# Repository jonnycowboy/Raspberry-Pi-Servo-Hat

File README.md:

Raspberry-Pi-Servo-Hat
======================
Will contain:
- 16 channels of PWM / Servo Control
- RS485 Servo Control
- CAN BUS communication
- - can berry
- -  http://skpang.co.uk/catalog/pican-canbus-board-for-raspberry-pi-p-1196.html
- I2C Communication

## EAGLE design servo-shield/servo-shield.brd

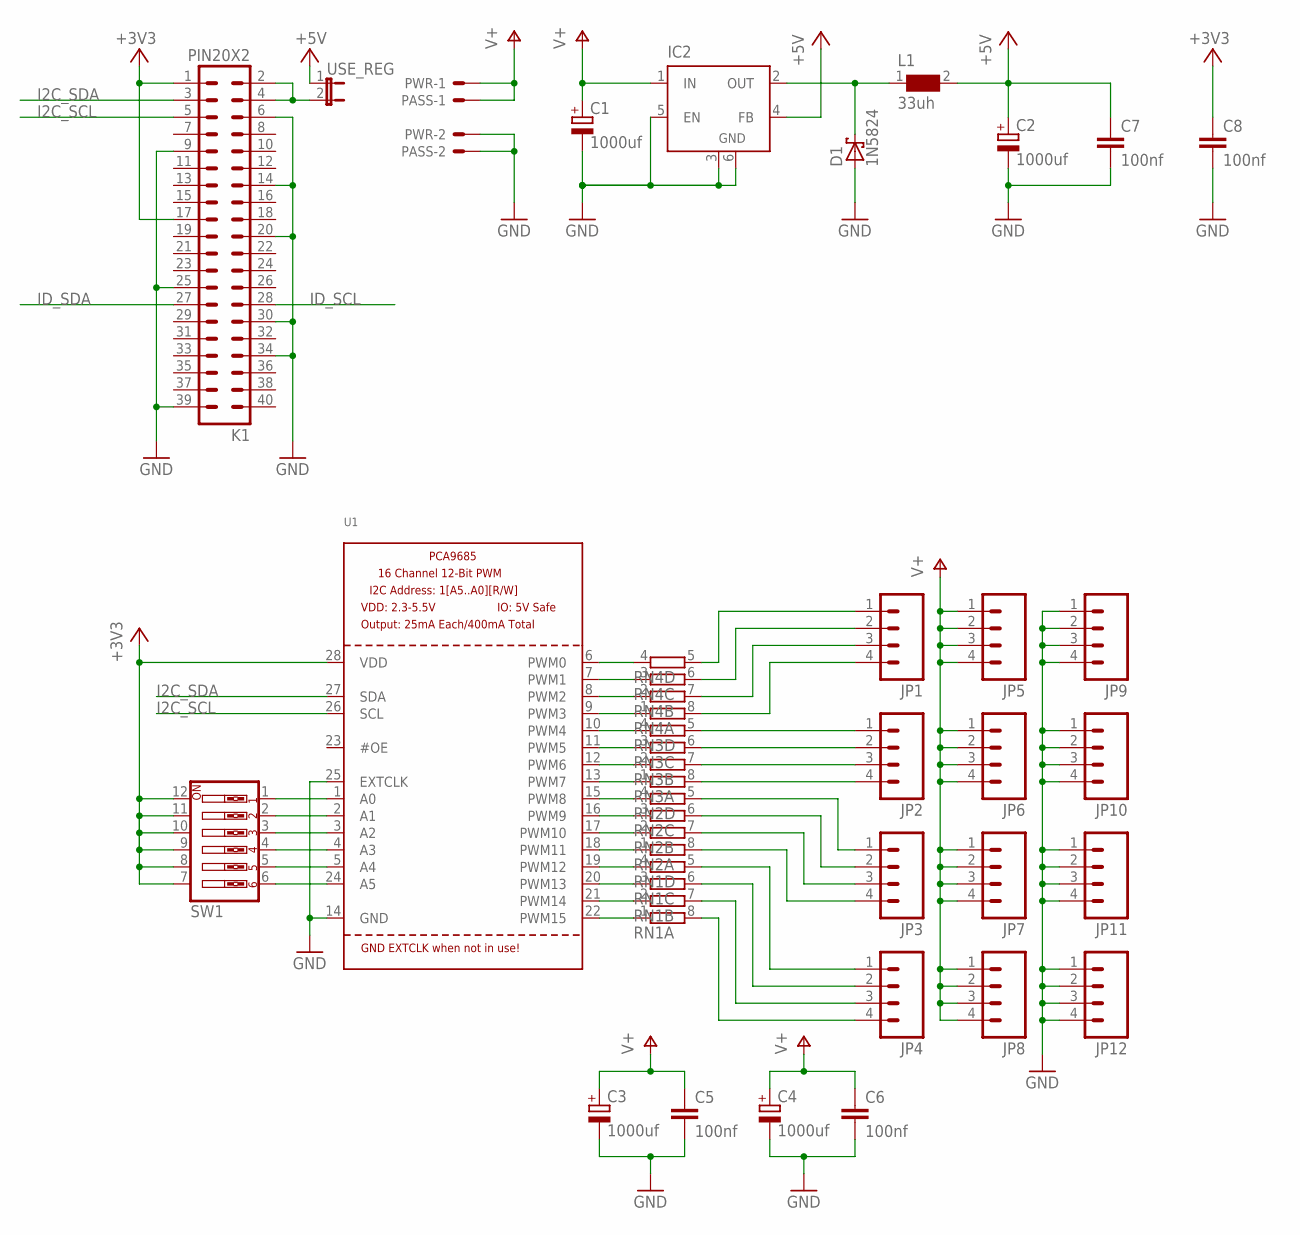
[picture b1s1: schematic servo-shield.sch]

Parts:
C1, C2, C3, C4: 1000uf; E3,5-8
C5, C6, C7, C8: 100nf; C025-030X050
D1: 1N5824; DO41-7.6
IC2: LM2596S; TO263-5
JP1, JP2, JP3, JP4, JP5, JP6, JP7, JP8, JP9, JP10, JP11, JP12: M04LOCK; 1X04_LOCK
K1: PIN20X2; PIN_20X2
L1: 33uh; WE-PD_1260/1245/1280/1210
PASS: 22-05-7028-02; 7395-02
PWR: 22-05-7028-02; 7395-02
RN1, RN2, RN3, RN4: 4R-NEXB38V; EXB38V
SW1: SW_DIP-6; EDG-06
U1: PCA9685; TSSOP28
USE_REG: JP1E; JP1

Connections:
+3V3: C8.1, K1.1, K1.17, SW1.7, SW1.8, SW1.9, SW1.10, SW1.11, SW1.12, U1.28 (VDD)
+5V: C2.+, C7.1, IC2.4 (FB), L1.2, USE_REG.1
GND: C1.-, C2.-, C3.-, C4.-, C5.2, C6.2, C7.2, C8.2, D1.A, IC2.3 (GND), IC2.5 (EN), IC2.6 (GND), JP9.1, JP9.2, JP9.3, JP9.4, JP10.1, JP10.2, JP10.3, JP10.4, JP11.1, JP11.2, JP11.3, JP11.4, JP12.1, JP12.2, JP12.3, JP12.4, K1.6, K1.9, K1.14, K1.20, K1.25, K1.30, K1.34, K1.39, PASS.2, PWR.2, U1.14 (GND), U1.25 (EXTCLK)
I2C_SCL: K1.5, U1.26 (SCL)
I2C_SDA: K1.3, U1.27 (SDA)
ID_SCL: K1.28
ID_SDA: K1.27
unnamed: RN2.3 (1), U1.16 (PWM9)
unnamed: RN2.4 (1), U1.15 (PWM8)
unnamed: RN3.1, U1.13 (PWM7)
unnamed: SW1.6, U1.24 (A5)
unnamed: JP1.4, RN4.8 (2)
unnamed: JP1.3, RN4.7 (2)
unnamed: JP1.2, RN4.6 (2)
unnamed: JP1.1, RN4.5 (2)
unnamed: JP3.1, RN2.5 (2)
unnamed: JP3.2, RN2.6 (2)
unnamed: SW1.1, U1.1 (A0)
unnamed: SW1.2, U1.2 (A1)
unnamed: SW1.5, U1.5 (A4)
unnamed: SW1.3, U1.3 (A2)
unnamed: SW1.4, U1.4 (A3)
unnamed: K1.2, K1.4, USE_REG.2
unnamed: JP3.3, RN2.7 (2)
unnamed: JP3.4, RN2.8 (2)
unnamed: JP4.1, RN1.5 (2)
unnamed: JP4.2, RN1.6 (2)
unnamed: JP4.3, RN1.7 (2)
unnamed: JP4.4, RN1.8 (2)
unnamed: RN1.1, U1.22 (PWM15)
unnamed: RN1.2 (1), U1.21 (PWM14)
unnamed: RN1.3 (1), U1.20 (PWM13)
unnamed: RN1.4 (1), U1.19 (PWM12)
unnamed: RN2.1, U1.18 (PWM11)
unnamed: RN2.2 (1), U1.17 (PWM10)
unnamed: RN3.2 (1), U1.12 (PWM6)
unnamed: RN3.3 (1), U1.11 (PWM5)
unnamed: RN3.4 (1), U1.10 (PWM4)
unnamed: RN4.1, U1.9 (PWM3)
unnamed: RN4.2 (1), U1.8 (PWM2)
unnamed: RN4.3 (1), U1.7 (PWM1)
unnamed: RN4.4 (1), U1.6 (PWM0)
unnamed: JP2.1, RN3.5 (2)
unnamed: JP2.4, RN3.8 (2)
unnamed: JP2.3, RN3.7 (2)
unnamed: JP2.2, RN3.6 (2)
V+: C1.+, C3.+, C4.+, C5.1, C6.1, IC2.1 (IN), JP5.1, JP5.2, JP5.3, JP5.4, JP6.1, JP6.2, JP6.3, JP6.4, JP7.1, JP7.2, JP7.3, JP7.4, JP8.1, JP8.2, JP8.3, JP8.4, PASS.1, PWR.1
VOUT: D1.C, IC2.2 (OUT), L1.1

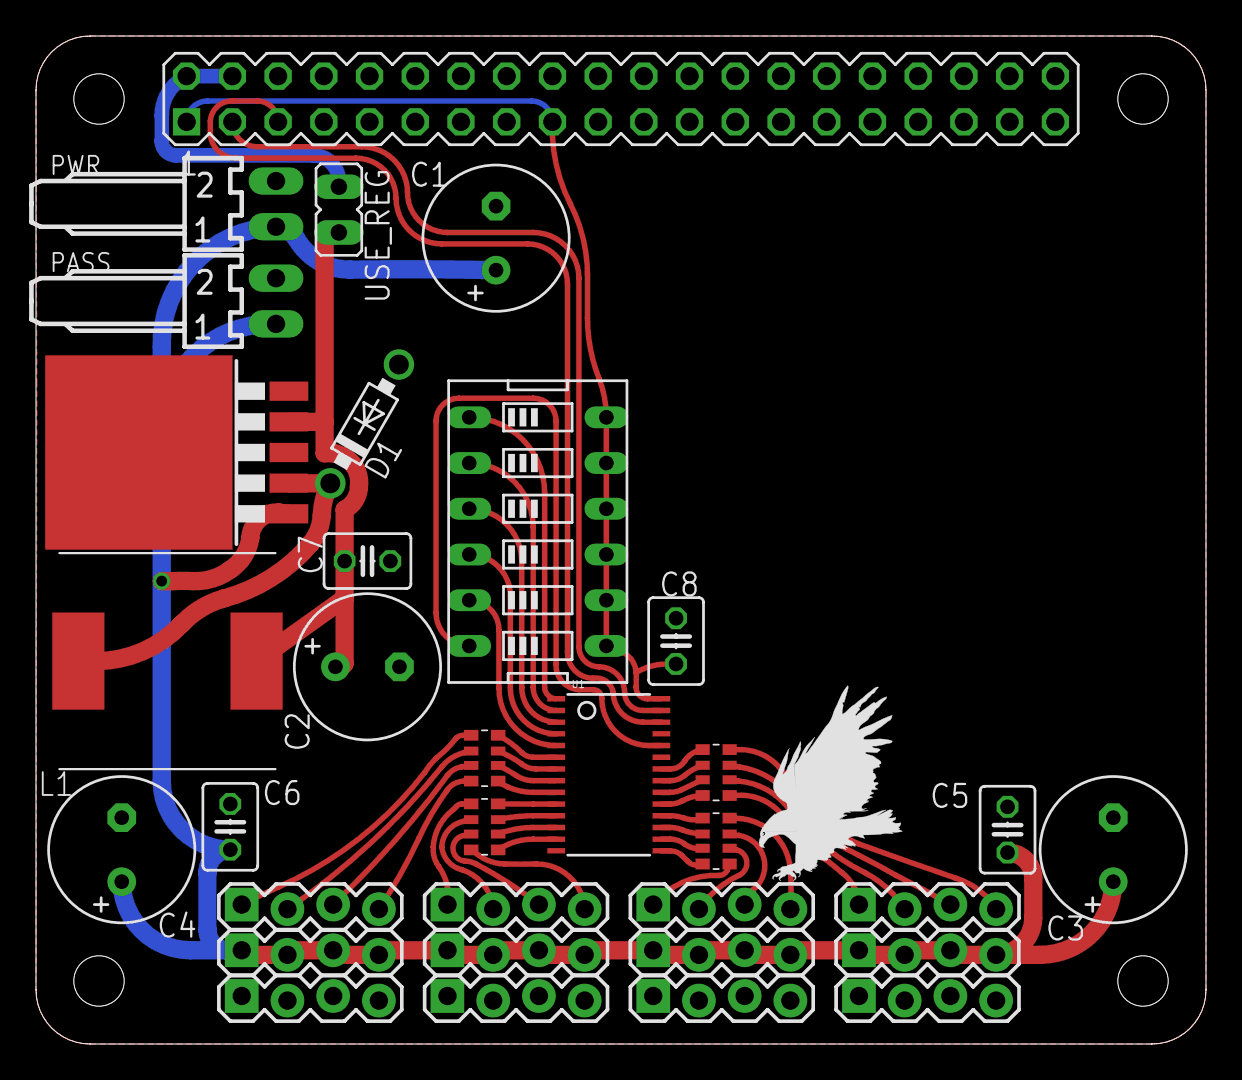
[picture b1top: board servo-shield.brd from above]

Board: 2 copper layers, 65.0 x 56.0 mm, 34 parts (0 on the bottom side), 46 nets.

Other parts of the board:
U$1: EAGLE-PLC-8MM

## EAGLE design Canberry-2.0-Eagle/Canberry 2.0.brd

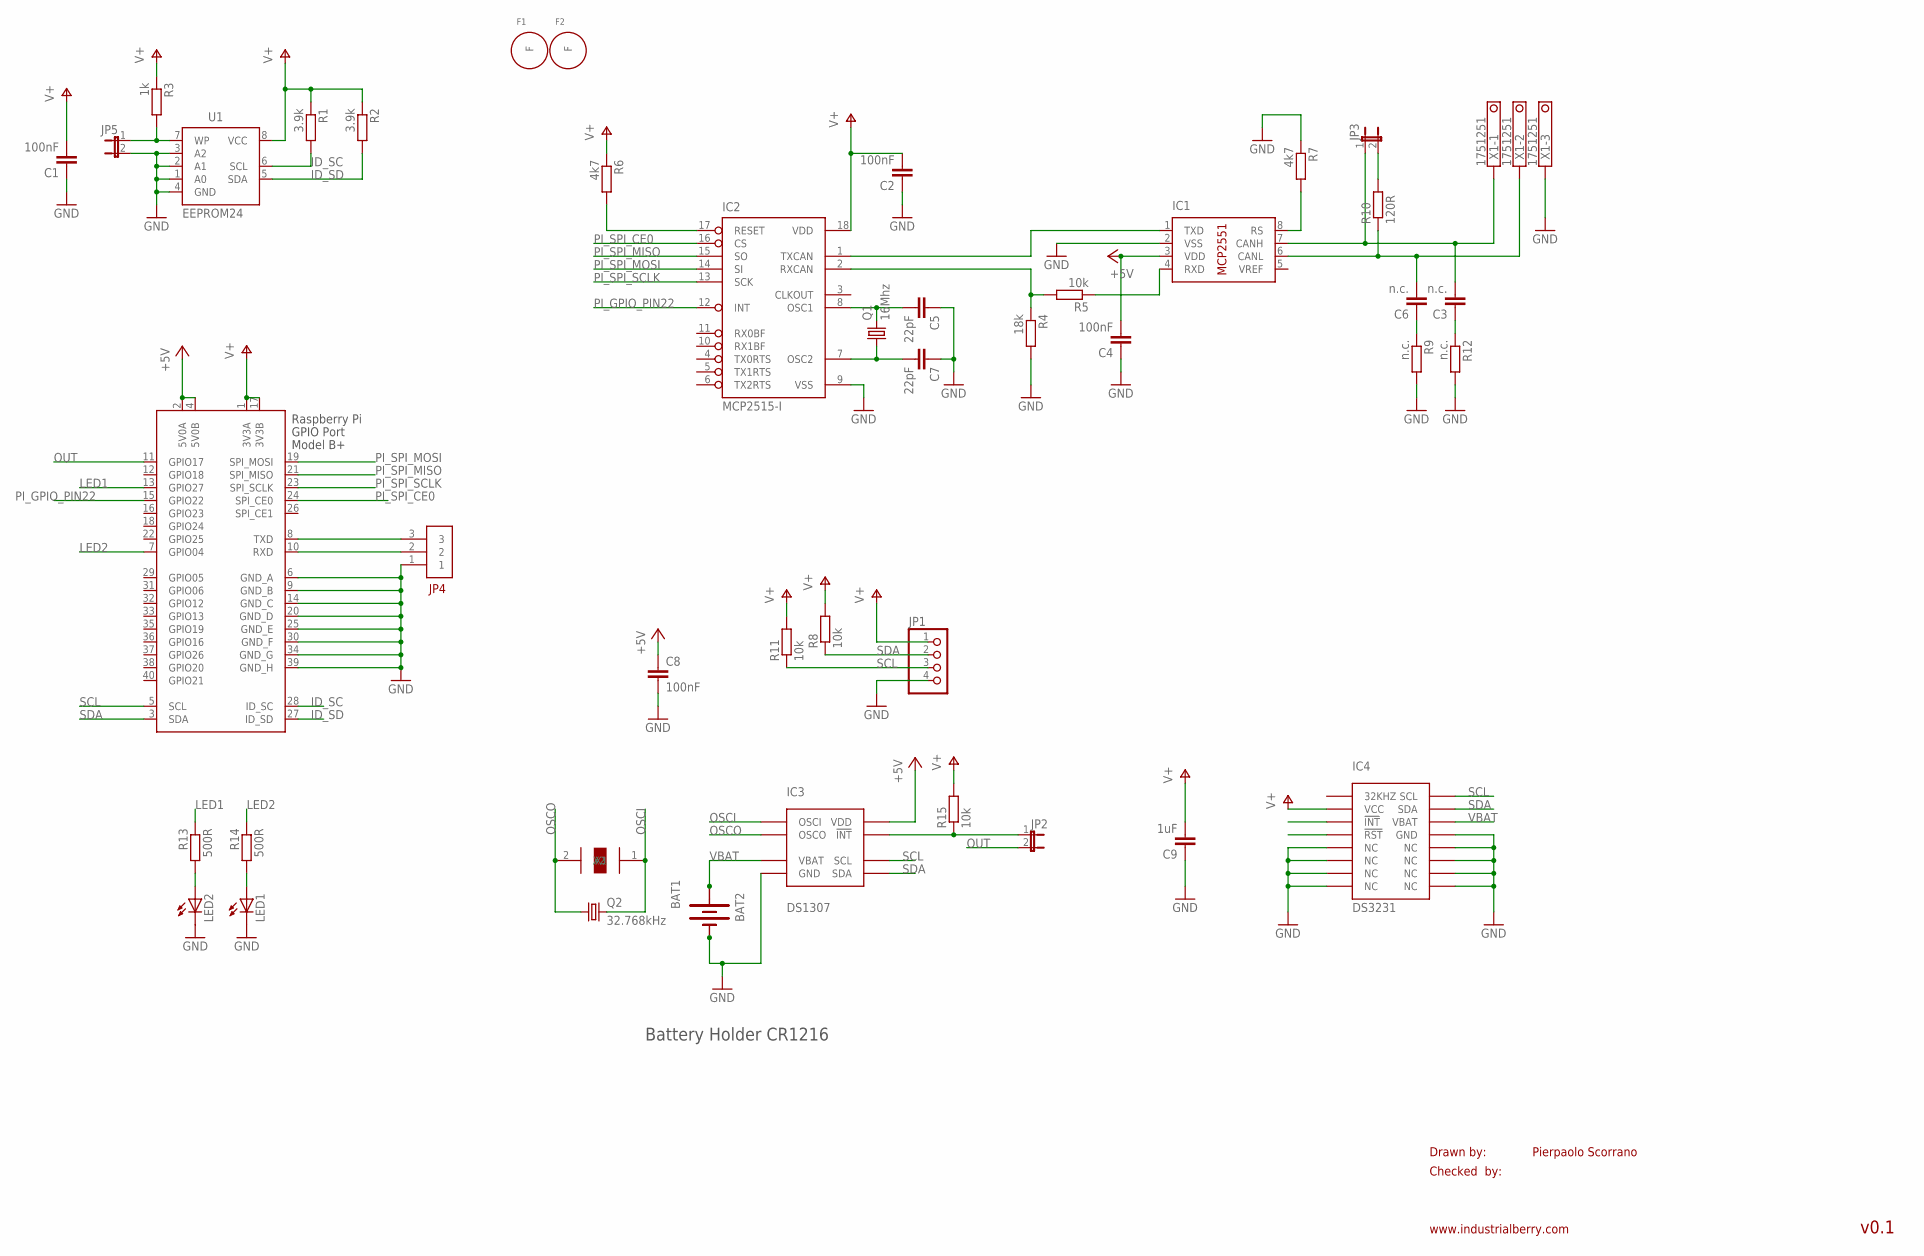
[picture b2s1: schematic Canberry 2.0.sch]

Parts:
BAT1: BATTERY12MM; BATTCON_12MM
BAT2: BATTERY12PTH; BATTCON_12MM_PTH
C1, C2, C4, C8: 100nF; C0603
C3, C6: n.c.; C0603
C5, C7: 22pF; C0603
C9: 1uF; C0603
F1, F2: FIDUCIAL-LAMINA
IC1: MCP2551; SO08
IC2: MCP2515-I; SO18L
IC3: DS1307; SO8
IC4: DS3231; SOIC-16W
JP1: PINHD-1X4; 1X04
JP2, JP3, JP5: JUMPER-2SMD-NO; SJ_2S-NO
JP4: MA03-1
LED1, LED2: LEDSMT1206; 1206
Q1: 16Mhz; CRYSTAL-SMD-10.5X4.8-2PIN
Q2: 32.768kHz; TC26H
R1, R2: 3.9k; R0603
R3: 1k; R0603
R4: 18k; R0603
R5, R8, R11, R15: 10k; R0603
R6, R7: 4k7; R0603
R9, R12: n.c.; R0603
R10: 120R; R0603
R13, R14: 500R; R0603
RPI1: RASPBERRY_HATSMT; CONNECTOR_B+_SMT
U1: EEPROM24; SOIC8
U$1: XTAL32K; FC-135
X1: 1751251

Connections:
+5V: C4.2, C8.1, IC1.3 (VDD), IC3.8 (VDD), RPI1.2 (5V0A), RPI1.4 (5V0B)
GND: BAT1.GND (-), BAT2.GND (-), C1.1, C2.1, C4.1, C5.1, C7.1, C8.2, C9.1, IC1.2 (VSS), IC2.9 (VSS), IC3.4 (GND), IC4.5 (NC), IC4.6 (NC), IC4.7 (NC), IC4.8 (NC), IC4.9 (NC), IC4.10 (NC), IC4.11 (NC), IC4.12 (NC), IC4.13 (GND), JP1.4, JP4.1, JP5.2, LED1.C, LED2.C, R4.2, R7.1, R9.2, R12.2, RPI1.6 (GND_A), RPI1.9 (GND_B), RPI1.14 (GND_C), RPI1.20 (GND_D), RPI1.25 (GND_E), RPI1.30 (GND_F), RPI1.34 (GND_G), RPI1.39 (GND_H), U1.1 (A0), U1.2 (A1), U1.3 (A2), U1.4 (GND), X1.3
ID_SC: R1.2, RPI1.28 (ID_SC), U1.6 (SCL)
ID_SD: R2.2, RPI1.27 (ID_SD), U1.5 (SDA)
LED1: R13.1, RPI1.13 (GPIO27)
LED2: R14.1, RPI1.7 (GPIO04)
unnamed: JP5.1, R3.2, U1.7 (WP)
unnamed: IC3.7 (!INT), IC4.3 (!INT), JP2.1, R15.1
unnamed: C7.2, IC2.7 (OSC2), Q1.P$1 (1)
unnamed: IC2.2 (RXCAN), R4.1, R5.2
unnamed: IC1.4 (RXD), R5.1
unnamed: IC1.1 (TXD), IC2.1 (TXCAN)
unnamed: IC1.8 (RS), R7.2
unnamed: IC2.17 (RESET), R6.2
unnamed: C6.1, R9.1
unnamed: C3.1, R12.1
unnamed: LED2.A, R13.2
unnamed: C5.2, IC2.8 (OSC1), Q1.P$2 (2)
unnamed: LED1.A, R14.2
unnamed: C3.2, IC1.7 (CANH), JP3.1, X1.1
unnamed: C6.2, IC1.6 (CANL), R10.1, X1.2
unnamed: JP3.2, R10.2
OSCI: IC3.1 (OSCI), Q2.2, U$1.1 (X1)
OSCO: IC3.2 (OSCO), Q2.1, U$1.2 (X2)
OUT: JP2.2, RPI1.11 (GPIO17)
PI_GPIO_PIN22: IC2.12 (INT), RPI1.15 (GPIO22)
PI_SPI_CE0: IC2.16 (CS), RPI1.24 (SPI_CE0)
PI_SPI_MISO: IC2.15 (SO), RPI1.21 (SPI_MISO)
PI_SPI_MOSI: IC2.14 (SI), RPI1.19 (SPI_MOSI)
PI_SPI_SCLK: IC2.13 (SCK), RPI1.23 (SPI_SCLK)
RXD: JP4.2, RPI1.10 (RXD)
SCL: IC3.6 (SCL), IC4.16 (SCL), JP1.3, R11.1, RPI1.5 (SCL)
SDA: IC3.5 (SDA), IC4.15 (SDA), JP1.2, R8.1, RPI1.3 (SDA)
TXD: JP4.3, RPI1.8 (TXD)
V+: C1.2, C2.2, C9.2, IC2.18 (VDD), IC4.2 (VCC), JP1.1, R1.1, R2.1, R3.1, R6.1, R8.2, R11.2, R15.2, RPI1.1 (3V3A), RPI1.17 (3V3B), U1.8 (VCC)
VBAT: BAT1.PWR@1 (+), BAT2.VCC@1 (+), IC3.3 (VBAT), IC4.14 (VBAT)

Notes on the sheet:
Drawn by:
Checked by:
www.industrialberry.com
Pierpaolo Scorrano
v0.1
Battery Holder CR1216

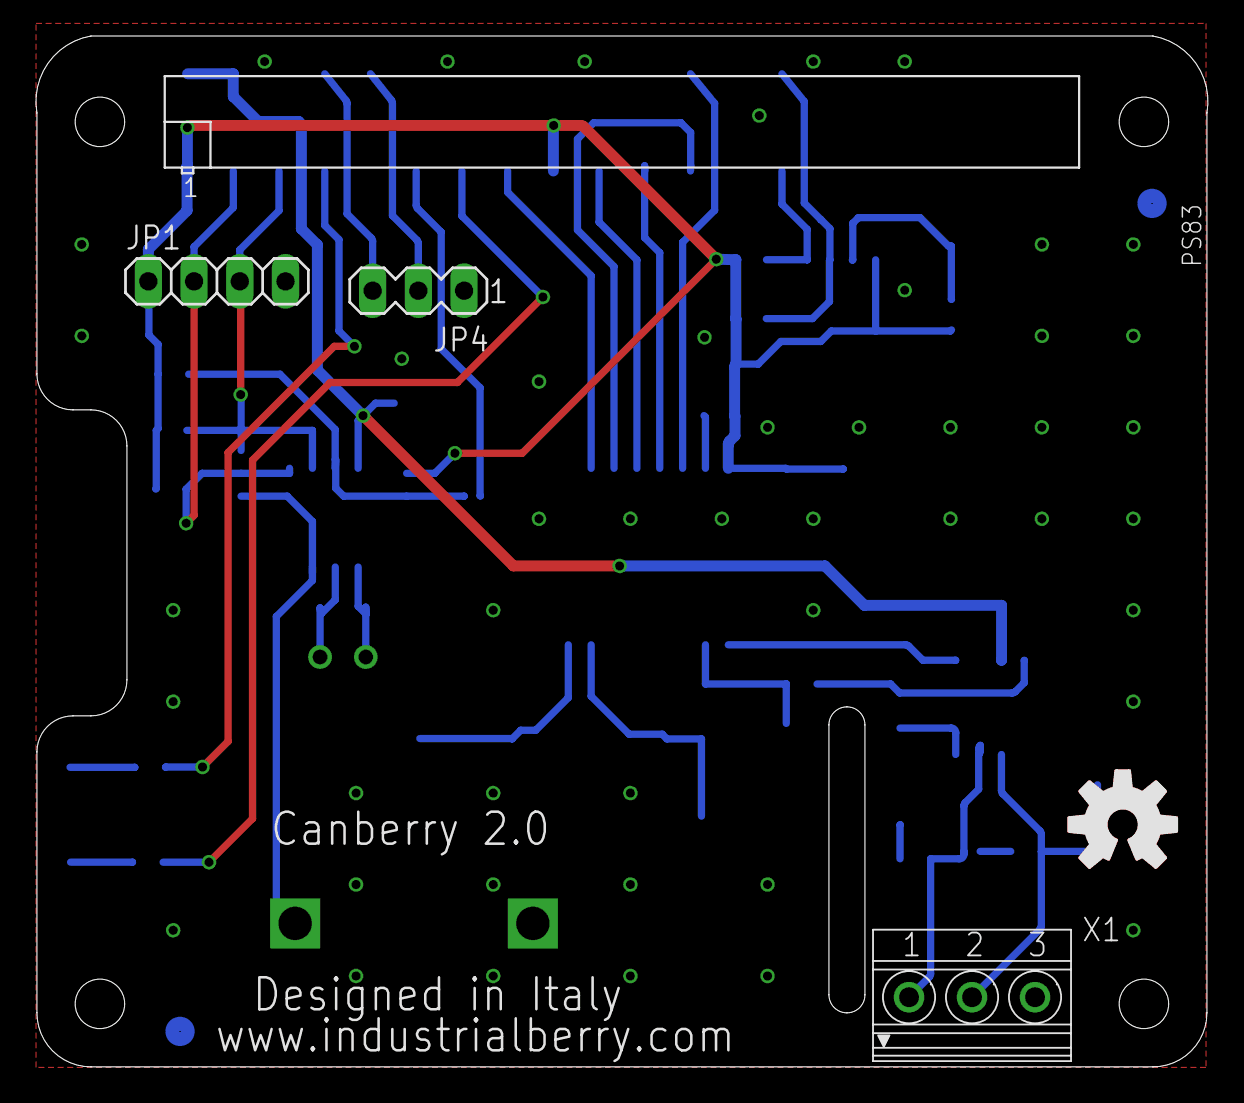
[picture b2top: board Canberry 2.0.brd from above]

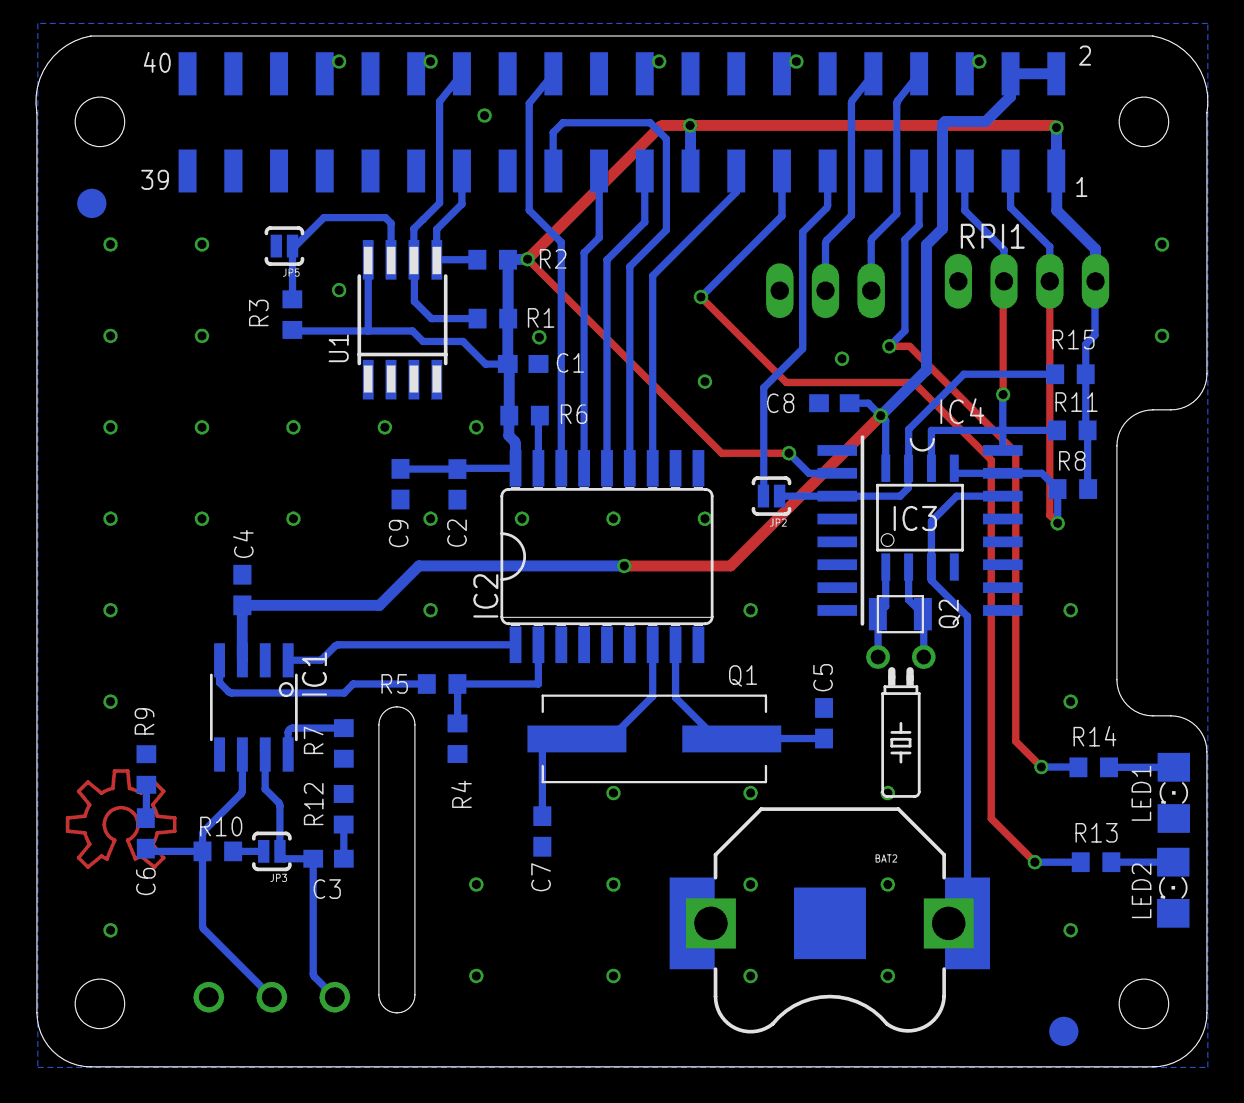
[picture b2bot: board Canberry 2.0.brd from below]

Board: 2 copper layers, 65.1 x 57.3 mm, 45 parts (41 on the bottom side), 36 nets.

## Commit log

2014-07-31 Change parts to using through-hole
2014-07-31 Remove cache files. Add them to gitignore
2014-07-31 Add PCA9685
2014-07-31 Finished current schematic.. Must add power supply and power regulation
2014-07-31 Added power connector + regulator
2014-07-31 Moved some parts and labels around
2014-08-01 Fix DRC errors. Wish I'd done that before ordering the blasted boards
2014-08-01 Made outputs curvy
2014-08-01 So bored. Curves. still passes DRC.
2014-08-01 Adding more to the gitignore
2014-08-01 Relocated capacitor, forgot to route its + terminal.
2014-09-06 This library has the inductor I want to use
2014-09-06 Mk2 board. Move servo connectors to longer edge, remove HAT related crap. We're not using it anyway, its just i2c. Fixed issues with regulator using a bogus inductor. Fixed power connector. Hopefully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
2014-09-06 Rejig schematic to fit on an A4 schematic sheet
2014-09-06 Move some parts labels about
2014-09-06 Rejig location of resistor networks
2014-09-06 Adding EagleCAD logo
2014-09-06 Updated eagle.epf
2014-09-06 add jumper to select if RaspberryPi uses servo board regulator.
2014-09-06 Rejigged to add passthru power connector
2014-09-06 Rotated D1 a bit to clear the DIP grid better.
2014-09-07 Rearranged C3 & C5 to be more pleasingly symmetrical
2015-03-15 added references and board examples

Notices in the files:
parts and their libraries:
SparkFun-Connectors: Licensing: Creative Commons ShareAlike 4.0 International - https://creativecommons.org/licenses/by-sa/4.0
